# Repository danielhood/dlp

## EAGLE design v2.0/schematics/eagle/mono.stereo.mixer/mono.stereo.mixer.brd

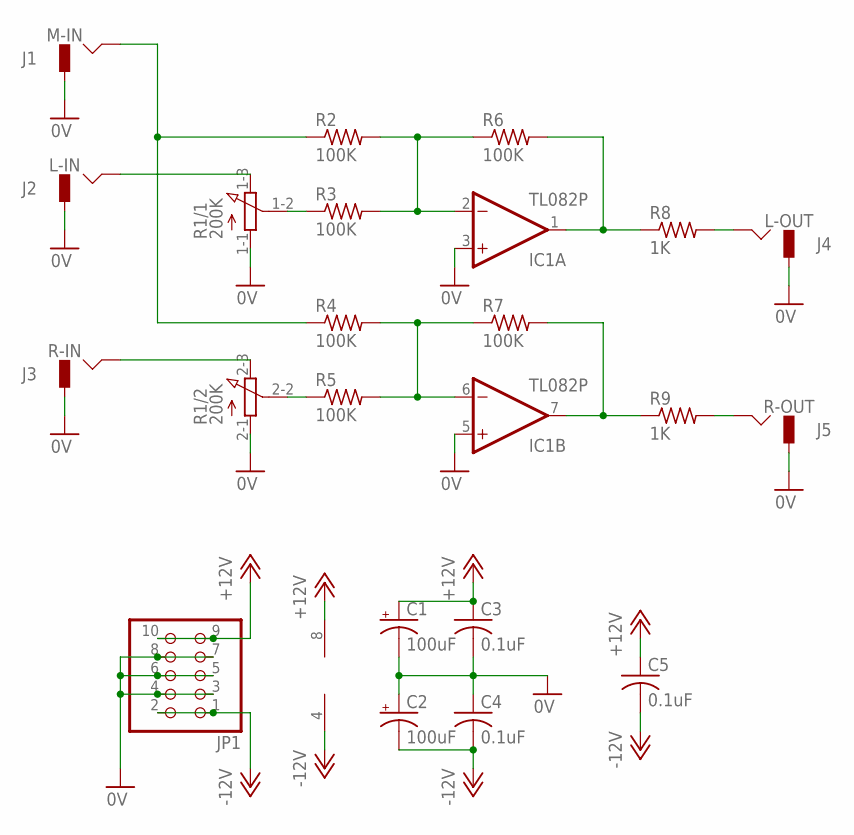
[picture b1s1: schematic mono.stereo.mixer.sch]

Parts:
C1, C2: 100uF; E2-5
C3, C4, C5: 0.1uF; C025-024X044
IC1: TL082P; DIL08
J1: M-IN; JACK-M
J2: L-IN; JACK-M
J3: R-IN; JACK-M
J4: L-OUT; JACK-M
J5: R-OUT; JACK-M
JP1: PINHD-2X5; 2X05
R1: 200K; 3RP/1610G
R2, R3, R4, R5, R6, R7: 100K; 0204/5
R8, R9: 1K; 0204/5

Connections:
0V: C1.-, C2.+, C3.2, C4.1, IC1.3 (+IN), IC1.5 (+IN), J1.GND, J2.GND, J3.GND, J4.GND, J5.GND, JP1.3, JP1.4, JP1.5, JP1.6, JP1.7, JP1.8, R1.1-1 (A), R1.2-1 (A)
+12V: C1.+, C3.1, C5.1, IC1.8 (V+), JP1.9, JP1.10
-12V: C2.-, C4.2, C5.2, IC1.4 (V-), JP1.1, JP1.2
unnamed: J1.HOT, R2.1, R4.1
unnamed: IC1.2 (-IN), R2.2, R3.2, R6.1
unnamed: IC1.6 (-IN), R4.2, R5.2, R7.1
unnamed: IC1.1 (OUT), R6.2, R8.1
unnamed: J4.HOT, R8.2
unnamed: IC1.7 (OUT), R7.2, R9.1
unnamed: J5.HOT, R9.2
unnamed: J2.HOT, R1.1-3 (E)
unnamed: J3.HOT, R1.2-3 (E)
unnamed: R1.2-2 (S), R5.1
unnamed: R1.1-2 (S), R3.1

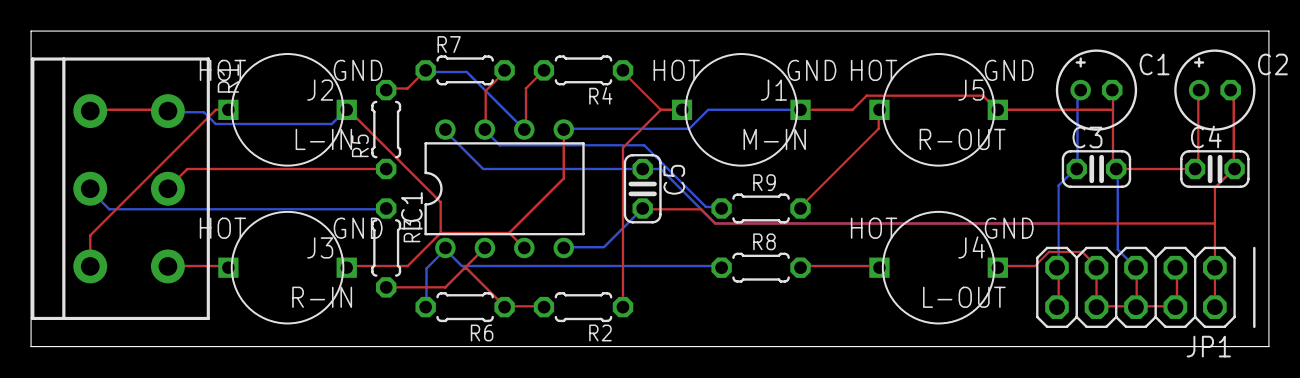
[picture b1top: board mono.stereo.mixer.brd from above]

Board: 2 copper layers, 79.7 x 20.3 mm, 21 parts (0 on the bottom side), 14 nets.

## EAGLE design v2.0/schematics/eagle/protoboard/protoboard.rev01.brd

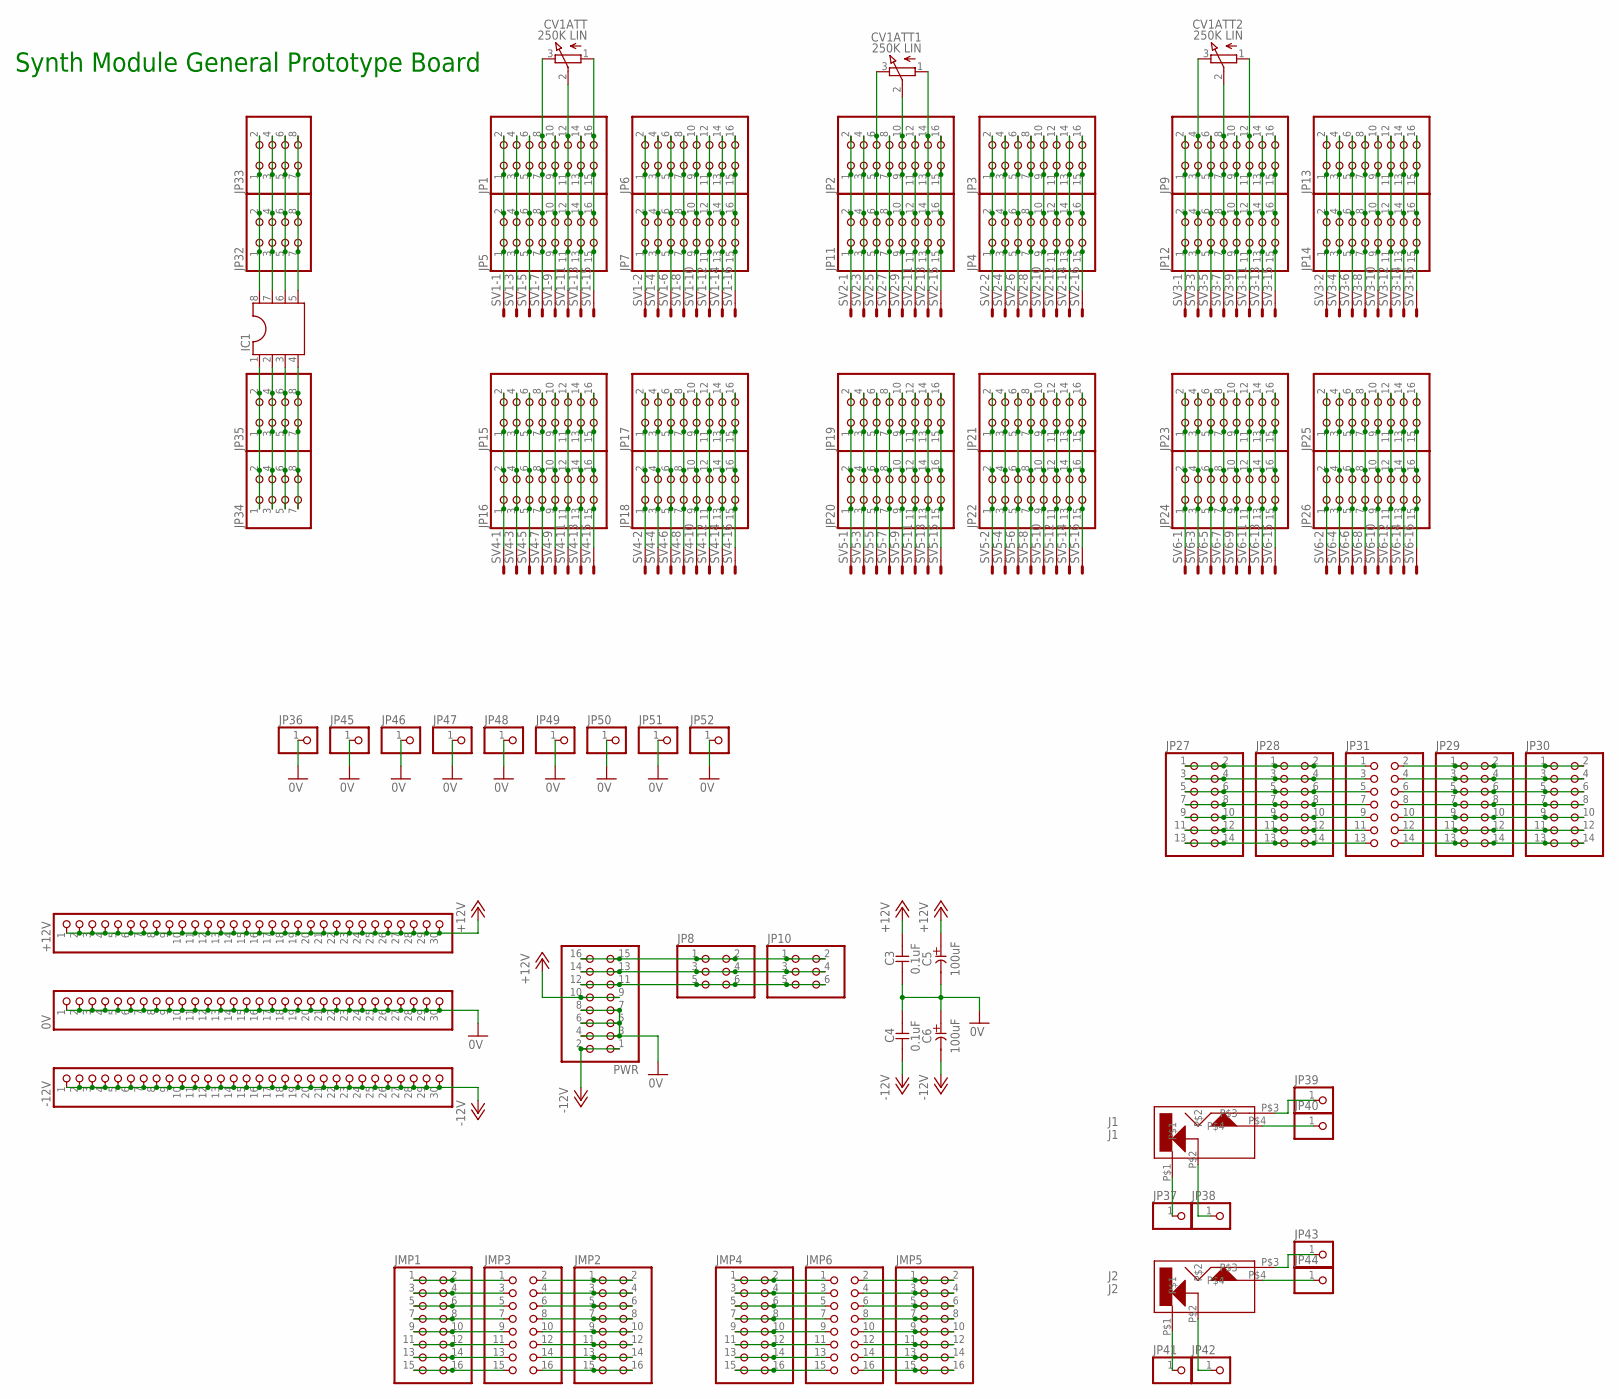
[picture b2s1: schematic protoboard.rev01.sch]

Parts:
0V: PINHD-1X30; 1X30
+12V: PINHD-1X30; 1X30
-12V: PINHD-1X30; 1X30
C3, C4: 0.1uF; C025-024X044
C5, C6: 100uF; E5-8,5
CV1ATT, CV1ATT1, CV1ATT2: 250K LIN; 3RP/1610N
IC1: DIL8S; SOCKET-08
J1: J1; CL1384
J2: J2; CL1384
JMP1, JMP2, JMP3, JMP4, JMP5, JMP6: PINHD-2X8; 2X08
JP1, JP2, JP3, JP4, JP5, JP6, JP7, JP9, JP11, JP12, JP13, JP14, JP15, JP16, JP17, JP18, JP19, JP20, JP21, JP22, JP23, JP24, JP25, JP26: PINHD-2X8; 2X08
JP8, JP10: PINHD-2X3; 2X03
JP27, JP28, JP29, JP30, JP31: PINHD-2X7; 2X07
JP32, JP33, JP34, JP35: PINHD-2X4; 2X04
JP36, JP37, JP38, JP39, JP40, JP41, JP42, JP43, JP44, JP45, JP46, JP47, JP48, JP49, JP50, JP51, JP52: PINHD-1X1; 1X01
PWR: PINHD-2X8; 2X08
SV1, SV2, SV3, SV4, SV5, SV6: 16E; 16P

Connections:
0V: 0V.1, 0V.2, 0V.3, 0V.4, 0V.5, 0V.6, 0V.7, 0V.8, 0V.9, 0V.10, 0V.11, 0V.12, 0V.13, 0V.14, 0V.15, 0V.16, 0V.17, 0V.18, 0V.19, 0V.20, 0V.21, 0V.22, 0V.23, 0V.24, 0V.25, 0V.26, 0V.27, 0V.28, 0V.29, 0V.30, C3.2, C4.1, C5.-, C6.+, JP36.1, JP45.1, JP46.1, JP47.1, JP48.1, JP49.1, JP50.1, JP51.1, JP52.1, PWR.3, PWR.4, PWR.5, PWR.6, PWR.7, PWR.8
+12V: +12V.1, +12V.2, +12V.3, +12V.4, +12V.5, +12V.6, +12V.7, +12V.8, +12V.9, +12V.10, +12V.11, +12V.12, +12V.13, +12V.14, +12V.15, +12V.16, +12V.17, +12V.18, +12V.19, +12V.20, +12V.21, +12V.22, +12V.23, +12V.24, +12V.25, +12V.26, +12V.27, +12V.28, +12V.29, +12V.30, C3.1, C5.+, PWR.9, PWR.10
-12V: -12V.1, -12V.2, -12V.3, -12V.4, -12V.5, -12V.6, -12V.7, -12V.8, -12V.9, -12V.10, -12V.11, -12V.12, -12V.13, -12V.14, -12V.15, -12V.16, -12V.17, -12V.18, -12V.19, -12V.20, -12V.21, -12V.22, -12V.23, -12V.24, -12V.25, -12V.26, -12V.27, -12V.28, -12V.29, -12V.30, C4.2, C6.-, PWR.1, PWR.2
unnamed: JP2.1, JP2.2, JP11.1, JP11.2, SV2.1
unnamed: JP3.1, JP3.2, JP4.1, JP4.2, SV2.2
unnamed: JP2.3, JP2.4, JP11.3, JP11.4, SV2.3
unnamed: CV1ATT1.3 (E), JP2.5, JP2.6, JP11.5, JP11.6, SV2.5
unnamed: JP2.7, JP2.8, JP11.7, JP11.8, SV2.7
unnamed: CV1ATT1.2 (S), JP2.9, JP2.10, JP11.9, JP11.10, SV2.9
unnamed: JP2.11, JP2.12, JP11.11, JP11.12, SV2.11
unnamed: CV1ATT1.1 (A), JP2.13, JP2.14, JP11.13, JP11.14, SV2.13
unnamed: JP3.3, JP3.4, JP4.3, JP4.4, SV2.4
unnamed: JP3.5, JP3.6, JP4.5, JP4.6, SV2.6
unnamed: JP3.7, JP3.8, JP4.7, JP4.8, SV2.8
unnamed: JP3.9, JP3.10, JP4.9, JP4.10, SV2.10
unnamed: JP3.11, JP3.12, JP4.11, JP4.12, SV2.12
unnamed: JP3.13, JP3.14, JP4.13, JP4.14, SV2.14
unnamed: JP3.15, JP3.16, JP4.15, JP4.16, SV2.16
unnamed: JP1.1, JP1.2, JP5.1, JP5.2, SV1.1
unnamed: JP1.3, JP1.4, JP5.3, JP5.4, SV1.3
unnamed: JP1.5, JP1.6, JP5.5, JP5.6, SV1.5
unnamed: CV1ATT.3 (E), JP1.7, JP1.8, JP5.7, JP5.8, SV1.7
unnamed: JP1.9, JP1.10, JP5.9, JP5.10, SV1.9
unnamed: CV1ATT.2 (S), JP1.11, JP1.12, JP5.11, JP5.12, SV1.11
unnamed: JP1.13, JP1.14, JP5.13, JP5.14, SV1.13
unnamed: CV1ATT.1 (A), JP1.15, JP1.16, JP5.15, JP5.16, SV1.15
unnamed: JP6.1, JP6.2, JP7.1, JP7.2, SV1.2
unnamed: JP6.3, JP6.4, JP7.3, JP7.4, SV1.4
unnamed: JP6.5, JP6.6, JP7.5, JP7.6, SV1.6
unnamed: JP6.7, JP6.8, JP7.7, JP7.8, SV1.8
unnamed: JP6.9, JP6.10, JP7.9, JP7.10, SV1.10
unnamed: JP6.11, JP6.12, JP7.11, JP7.12, SV1.12
unnamed: JP2.15, JP2.16, JP11.15, JP11.16, SV2.15
unnamed: JP6.13, JP6.14, JP7.13, JP7.14, SV1.14
unnamed: JP6.15, JP6.16, JP7.15, JP7.16, SV1.16
unnamed: JP9.1, JP9.2, JP12.1, JP12.2, SV3.1
unnamed: CV1ATT2.3 (E), JP9.3, JP9.4, JP12.3, JP12.4, SV3.3
unnamed: JP9.5, JP9.6, JP12.5, JP12.6, SV3.5
unnamed: CV1ATT2.2 (S), JP9.7, JP9.8, JP12.7, JP12.8, SV3.7
unnamed: JP9.9, JP9.10, JP12.9, JP12.10, SV3.9
unnamed: CV1ATT2.1 (A), JP9.11, JP9.12, JP12.11, JP12.12, SV3.11
unnamed: JP9.13, JP9.14, JP12.13, JP12.14, SV3.13
unnamed: JP9.15, JP9.16, JP12.15, JP12.16, SV3.15
unnamed: JP13.1, JP13.2, JP14.1, JP14.2, SV3.2
unnamed: JP13.3, JP13.4, JP14.3, JP14.4, SV3.4
unnamed: JP13.5, JP13.6, JP14.5, JP14.6, SV3.6
unnamed: JP13.7, JP13.8, JP14.7, JP14.8, SV3.8
unnamed: JP13.9, JP13.10, JP14.9, JP14.10, SV3.10
unnamed: JP13.11, JP13.12, JP14.11, JP14.12, SV3.12
unnamed: JP13.13, JP13.14, JP14.13, JP14.14, SV3.14
unnamed: JP13.15, JP13.16, JP14.15, JP14.16, SV3.16
unnamed: JP15.1, JP15.2, JP16.1, JP16.2, SV4.1
unnamed: JP15.3, JP15.4, JP16.3, JP16.4, SV4.3
unnamed: JP15.5, JP15.6, JP16.5, JP16.6, SV4.5
unnamed: JP15.7, JP15.8, JP16.7, JP16.8, SV4.7
unnamed: JP15.9, JP15.10, JP16.9, JP16.10, SV4.9
unnamed: JP15.11, JP15.12, JP16.11, JP16.12, SV4.11
unnamed: JP15.13, JP15.14, JP16.13, JP16.14, SV4.13
unnamed: JP15.15, JP15.16, JP16.15, JP16.16, SV4.15
unnamed: JP17.1, JP17.2, JP18.1, JP18.2, SV4.2
unnamed: JP17.3, JP17.4, JP18.3, JP18.4, SV4.4
unnamed: JP17.5, JP17.6, JP18.5, JP18.6, SV4.6
unnamed: JP17.7, JP17.8, JP18.7, JP18.8, SV4.8
unnamed: JP17.9, JP17.10, JP18.9, JP18.10, SV4.10
unnamed: JP17.11, JP17.12, JP18.11, JP18.12, SV4.12
unnamed: JP17.13, JP17.14, JP18.13, JP18.14, SV4.14
unnamed: JP17.15, JP17.16, JP18.15, JP18.16, SV4.16
unnamed: JP19.1, JP19.2, JP20.1, JP20.2, SV5.1
unnamed: JP19.3, JP19.4, JP20.3, JP20.4, SV5.3
unnamed: JP19.5, JP19.6, JP20.5, JP20.6, SV5.5
unnamed: JP19.7, JP19.8, JP20.7, JP20.8, SV5.7
unnamed: JP19.9, JP19.10, JP20.9, JP20.10, SV5.9
unnamed: JP19.11, JP19.12, JP20.11, JP20.12, SV5.11
unnamed: JP19.13, JP19.14, JP20.13, JP20.14, SV5.13
unnamed: JP19.15, JP19.16, JP20.15, JP20.16, SV5.15
unnamed: JP21.1, JP21.2, JP22.1, JP22.2, SV5.2
unnamed: JP21.3, JP21.4, JP22.3, JP22.4, SV5.4
unnamed: JP21.5, JP21.6, JP22.5, JP22.6, SV5.6
unnamed: JP21.7, JP21.8, JP22.7, JP22.8, SV5.8
unnamed: JP21.9, JP21.10, JP22.9, JP22.10, SV5.10
unnamed: JP21.11, JP21.12, JP22.11, JP22.12, SV5.12
unnamed: JP21.13, JP21.14, JP22.13, JP22.14, SV5.14
unnamed: JP21.15, JP21.16, JP22.15, JP22.16, SV5.16
unnamed: JP23.1, JP23.2, JP24.1, JP24.2, SV6.1
unnamed: JP23.3, JP23.4, JP24.3, JP24.4, SV6.3
unnamed: JP23.5, JP23.6, JP24.5, JP24.6, SV6.5
unnamed: JP23.7, JP23.8, JP24.7, JP24.8, SV6.7
unnamed: JP23.9, JP23.10, JP24.9, JP24.10, SV6.9
unnamed: JP23.11, JP23.12, JP24.11, JP24.12, SV6.11
unnamed: JP23.13, JP23.14, JP24.13, JP24.14, SV6.13
unnamed: JP23.15, JP23.16, JP24.15, JP24.16, SV6.15
unnamed: JP25.1, JP25.2, JP26.1, JP26.2, SV6.2
unnamed: JP25.3, JP25.4, JP26.3, JP26.4, SV6.4
unnamed: JP25.5, JP25.6, JP26.5, JP26.6, SV6.6
unnamed: JP25.7, JP25.8, JP26.7, JP26.8, SV6.8
unnamed: JP25.9, JP25.10, JP26.9, JP26.10, SV6.10
unnamed: JP25.11, JP25.12, JP26.11, JP26.12, SV6.12
unnamed: JP25.13, JP25.14, JP26.13, JP26.14, SV6.14
unnamed: JP25.15, JP25.16, JP26.15, JP26.16, SV6.16
unnamed: J1.P$1, JP37.1
unnamed: J1.P$2, JP38.1
unnamed: J2.P$1, JP41.1
unnamed: J2.P$2, JP42.1
unnamed: JMP1.1, JMP1.2, JMP3.1
unnamed: JMP1.3, JMP1.4, JMP3.3
unnamed: JMP1.5, JMP1.6, JMP3.5
unnamed: JMP1.7, JMP1.8, JMP3.7
unnamed: JMP1.9, JMP1.10, JMP3.9
unnamed: JMP1.11, JMP1.12, JMP3.11
unnamed: JMP1.13, JMP1.14, JMP3.13
unnamed: JMP1.15, JMP1.16, JMP3.15
unnamed: JMP2.1, JMP2.2, JMP3.2
unnamed: JMP2.3, JMP2.4, JMP3.4
unnamed: JMP2.5, JMP2.6, JMP3.6
unnamed: JMP2.7, JMP2.8, JMP3.8
unnamed: JMP2.9, JMP2.10, JMP3.10
unnamed: JMP2.11, JMP2.12, JMP3.12
unnamed: JMP2.13, JMP2.14, JMP3.14
unnamed: JMP2.15, JMP2.16, JMP3.16
unnamed: JMP4.1, JMP4.2, JMP6.1
unnamed: JMP4.3, JMP4.4, JMP6.3
unnamed: JMP4.5, JMP4.6, JMP6.5
unnamed: JMP4.7, JMP4.8, JMP6.7
unnamed: JMP4.9, JMP4.10, JMP6.9
unnamed: JMP4.11, JMP4.12, JMP6.11
unnamed: JMP4.13, JMP4.14, JMP6.13
unnamed: JMP4.15, JMP4.16, JMP6.15
unnamed: JMP5.1, JMP5.2, JMP6.2
unnamed: JMP5.3, JMP5.4, JMP6.4
unnamed: JMP5.5, JMP5.6, JMP6.6
unnamed: JMP5.7, JMP5.8, JMP6.8
unnamed: JMP5.9, JMP5.10, JMP6.10
unnamed: JMP5.11, JMP5.12, JMP6.12
unnamed: JMP5.13, JMP5.14, JMP6.14
unnamed: JMP5.15, JMP5.16, JMP6.16
unnamed: JP27.1, JP27.2, JP28.1, JP28.2, JP31.1
unnamed: JP27.3, JP27.4, JP28.3, JP28.4, JP31.3
unnamed: JP27.5, JP27.6, JP28.5, JP28.6, JP31.5
unnamed: JP27.7, JP27.8, JP28.7, JP28.8, JP31.7
unnamed: JP27.9, JP27.10, JP28.9, JP28.10, JP31.9
unnamed: JP27.11, JP27.12, JP28.11, JP28.12, JP31.11
unnamed: JP27.13, JP27.14, JP28.13, JP28.14, JP31.13
unnamed: IC1.8, JP32.1, JP32.2, JP33.1, JP33.2
unnamed: IC1.7, JP32.3, JP32.4, JP33.3, JP33.4
unnamed: IC1.6, JP32.5, JP32.6, JP33.5, JP33.6
unnamed: IC1.5, JP32.7, JP32.8, JP33.7, JP33.8
unnamed: J2.P$3, JP43.1
unnamed: J2.P$4, JP44.1
unnamed: J1.P$4, JP40.1
unnamed: JP29.1, JP29.2, JP30.1, JP30.2, JP31.2
unnamed: JP29.3, JP29.4, JP30.3, JP30.4, JP31.4
unnamed: JP29.5, JP29.6, JP30.5, JP30.6, JP31.6
unnamed: JP29.7, JP29.8, JP30.7, JP30.8, JP31.8
unnamed: JP29.9, JP29.10, JP30.9, JP30.10, JP31.10
unnamed: JP29.11, JP29.12, JP30.11, JP30.12, JP31.12
unnamed: JP29.13, JP29.14, JP30.13, JP30.14, JP31.14
unnamed: J1.P$3, JP39.1
unnamed: IC1.1, JP34.1, JP34.2, JP35.1, JP35.2
unnamed: IC1.2, JP34.3, JP34.4, JP35.3, JP35.4
unnamed: IC1.3, JP34.5, JP34.6, JP35.5, JP35.6
unnamed: IC1.4, JP34.7, JP34.8, JP35.7, JP35.8
unnamed: JP8.5, JP8.6, JP10.5, JP10.6, PWR.11, PWR.12
unnamed: JP8.1, JP8.2, JP10.1, JP10.2, PWR.15, PWR.16
unnamed: JP8.3, JP8.4, JP10.3, JP10.4, PWR.13, PWR.14

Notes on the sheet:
Synth Module General Prototype Board

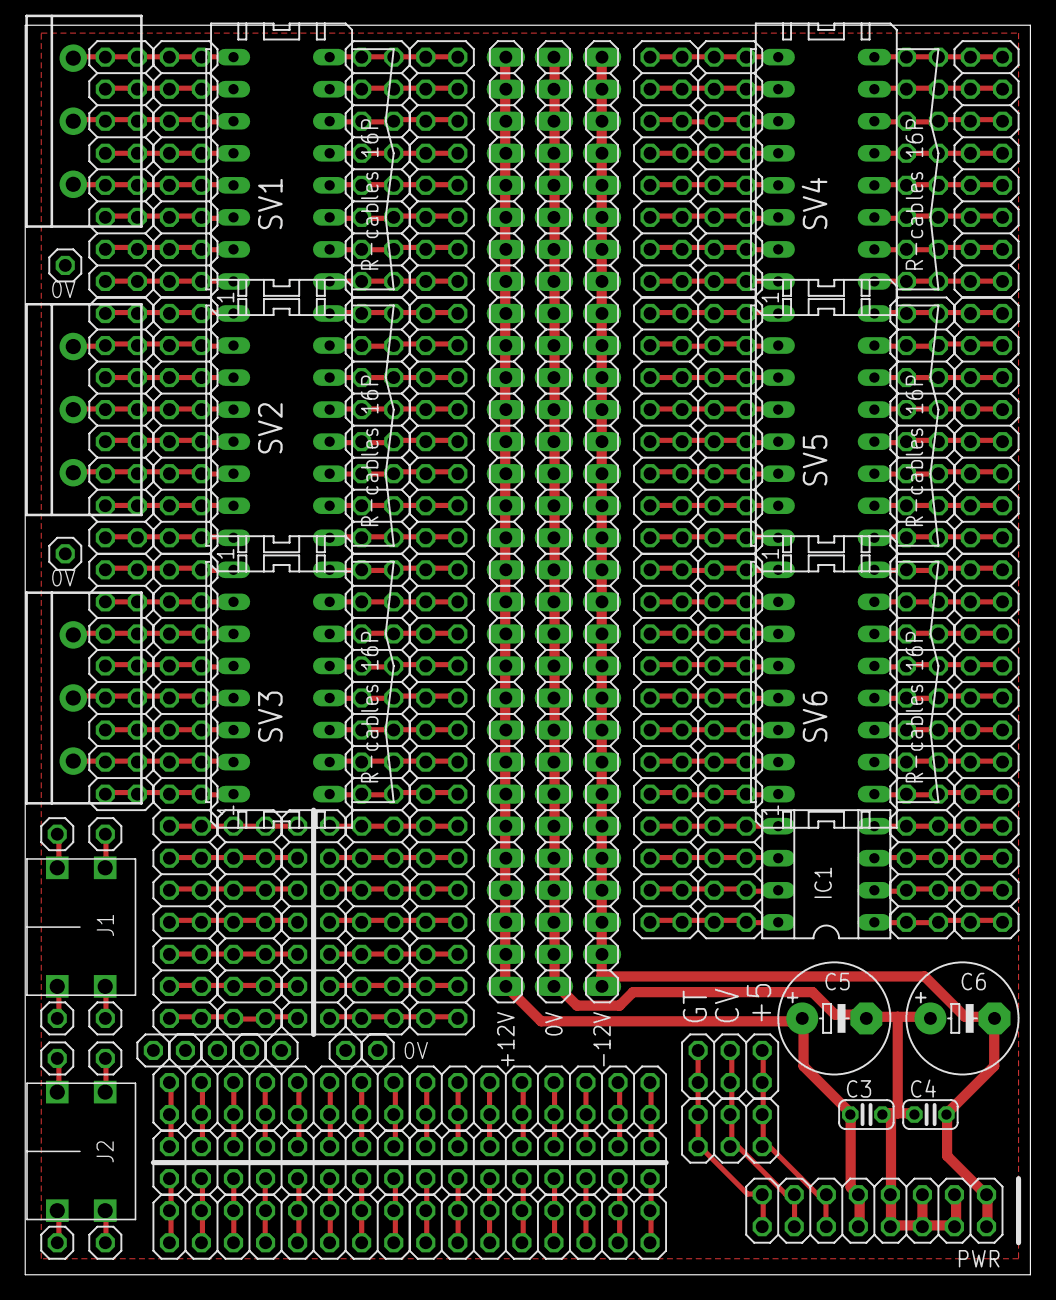
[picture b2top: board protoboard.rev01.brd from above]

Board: 2 copper layers, 79.7 x 99.0 mm, 78 parts (1 on the bottom side), 164 nets.

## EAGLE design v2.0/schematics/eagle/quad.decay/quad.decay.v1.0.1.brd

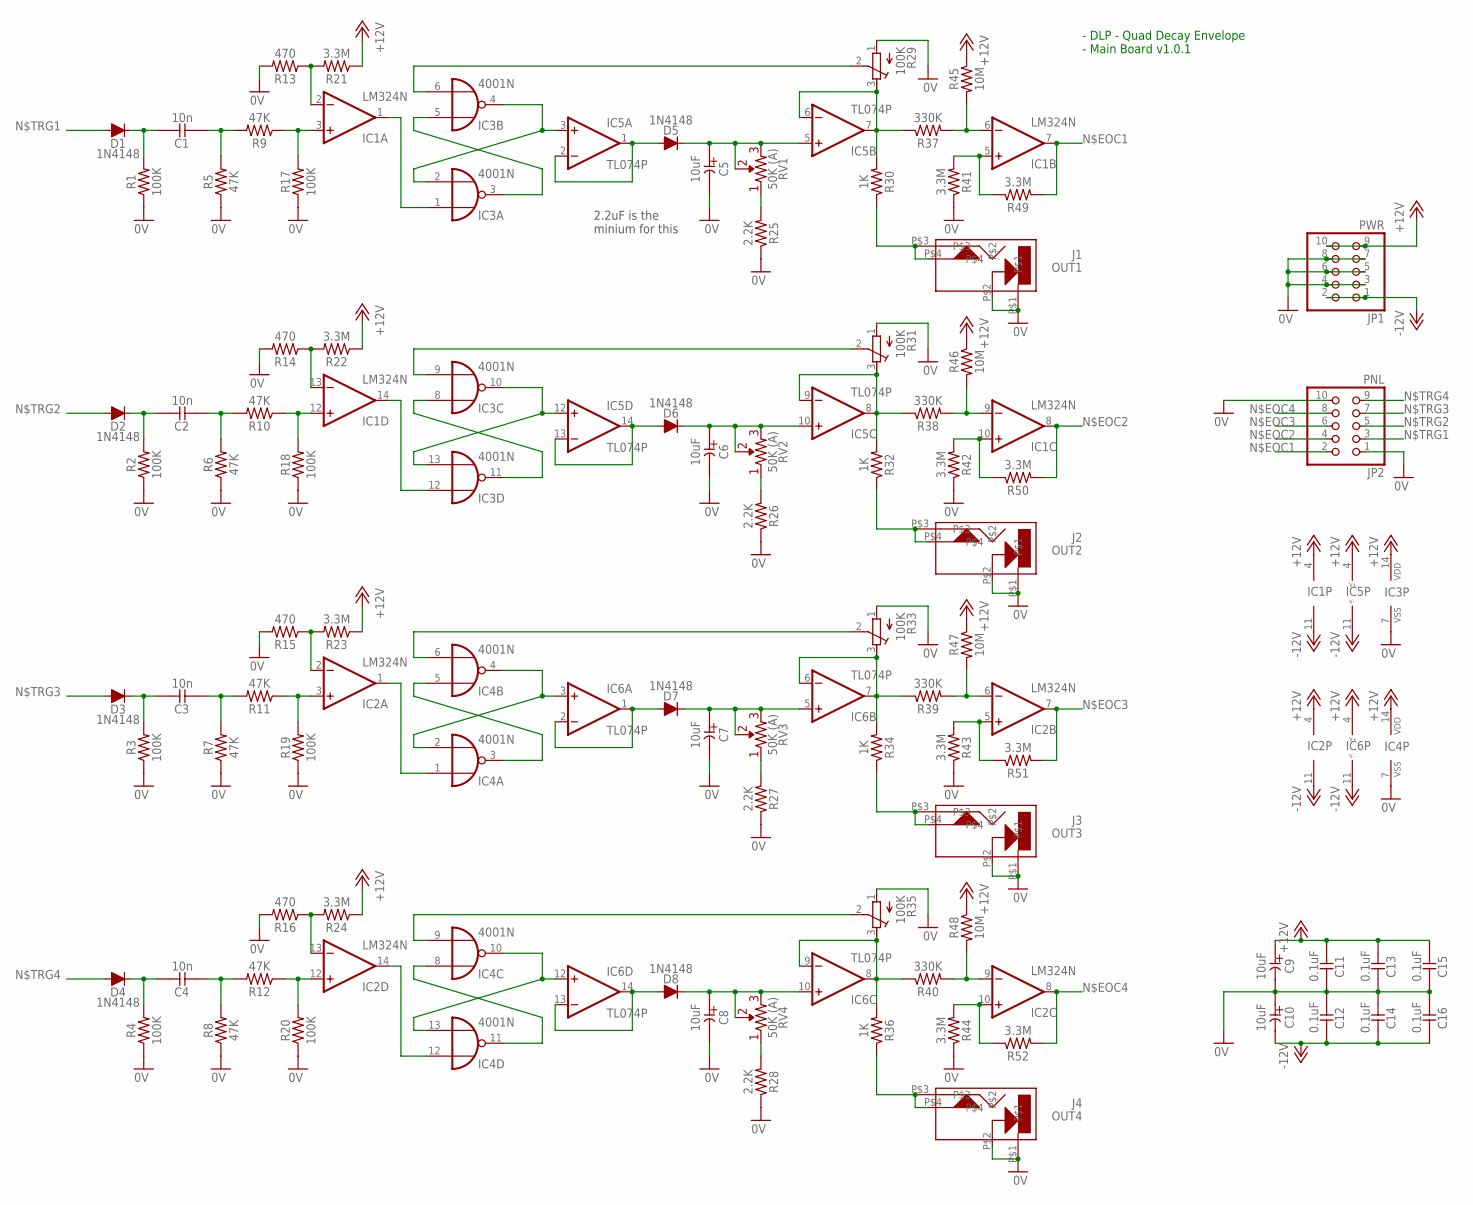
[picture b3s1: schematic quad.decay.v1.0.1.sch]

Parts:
C1, C2, C3, C4: 10n; C025-024X044
C5, C6, C7, C8, C9, C10: 10uF; E2-5
C11, C12, C13, C14, C15, C16: 0.1uF; C025-024X044
D1, D2, D3, D4, D5, D6, D7, D8: 1N4148; DO34-5
IC1, IC2: LM324N; DIL14
IC3, IC4: 4001N; DIL14
IC5, IC6: TL074P; DIL14
J1: OUT1; CL1384
J2: OUT2; CL1384
J3: OUT3; CL1384
J4: OUT4; CL1384
JP1: PWR; 2X05
JP2: PNL; 2X05
R1, R2, R3, R4, R17, R18, R19, R20: 100K; 0207/7
R5, R6, R7, R8, R9, R10, R11, R12: 47K; 0207/7
R13, R14, R15, R16: 470; 0207/7
R21, R22, R23, R24, R41, R42, R43, R44, R49, R50, R51, R52: 3.3M; 0207/7
R25, R26, R27, R28: 2.2K; 0207/7
R29, R31, R33, R35: 100K; RTRIM3339P
R30, R32, R34, R36: 1K; 0207/7
R37, R38, R39, R40: 330K; 0207/7
R45, R46, R47, R48: 10M; 0207/7
RV1, RV2, RV3, RV4: 50K (A); R-VAR

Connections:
0V: C5.-, C6.-, C7.-, C8.-, C9.-, C10.+, C11.1, C12.2, C13.1, C14.2, C15.1, C16.2, IC3.7 (VSS), IC4.7 (VSS), J1.P$1, J1.P$2, J2.P$1, J2.P$2, J3.P$1, J3.P$2, J4.P$1, J4.P$2, JP1.3, JP1.4, JP1.5, JP1.6, JP1.7, JP1.8, JP2.1, JP2.10, R1.1, R2.1, R3.1, R4.1, R5.1, R6.1, R7.1, R8.1, R13.2, R14.2, R15.2, R16.2, R17.1, R18.1, R19.1, R20.1, R25.1, R26.1, R27.1, R28.1, R29.1 (A), R31.1 (A), R33.1 (A), R35.1 (A), R41.1, R42.1, R43.1, R44.1
+12V: C9.+, C11.2, C13.2, C15.2, IC1.4 (V+), IC2.4 (V+), IC3.14 (VDD), IC4.14 (VDD), IC5.4 (V+), IC6.4 (V+), JP1.9, JP1.10, R21.1, R22.1, R23.1, R24.1, R45.1, R46.1, R47.1, R48.1
-12V: C10.-, C12.1, C14.1, C16.1, IC1.11 (V-), IC2.11 (V-), IC5.11 (V-), IC6.11 (V-), JP1.1, JP1.2
unnamed: R25.2, RV1.R1 (1)
unnamed: IC1.6 (-IN), R37.2, R45.2
unnamed: IC1.5 (+IN), R41.2, R49.1
unnamed: IC3.3 (O), IC3.5 (I0)
unnamed: IC3.8 (I0), IC3.11 (O)
unnamed: IC3.10 (O), IC3.13 (I1), IC5.12 (+IN)
unnamed: C2.1, D2.C, R2.2
unnamed: C2.2, R6.2, R10.2
unnamed: IC1.12 (+IN), R10.1, R18.2
unnamed: IC3.2 (I1), IC3.4 (O), IC5.3 (+IN)
unnamed: IC1.13 (-IN), R14.1, R22.2
unnamed: D5.A, IC5.1 (OUT), IC5.2 (-IN)
unnamed: C1.1, D1.C, R1.2
unnamed: C1.2, R5.2, R9.2
unnamed: IC1.3 (+IN), R9.1, R17.2
unnamed: IC1.2 (-IN), R13.1, R21.2
unnamed: IC1.1 (OUT), IC3.1 (I0)
unnamed: IC5.6 (-IN), IC5.7 (OUT), R29.3 (E), R30.2, R37.1
unnamed: J1.P$3, J1.P$4, R30.1
unnamed: IC3.6 (I1), R29.2 (S)
unnamed: IC1.14 (OUT), IC3.12 (I0)
unnamed: D6.A, IC5.13 (-IN), IC5.14 (OUT)
unnamed: IC5.8 (OUT), IC5.9 (-IN), R31.3 (E), R32.2, R38.1
unnamed: J2.P$3, J2.P$4, R32.1
unnamed: IC3.9 (I1), R31.2 (S)
unnamed: C6.+, D6.C, IC5.10 (+IN), RV2.R2 (2), RV2.VAR
unnamed: R26.2, RV2.R1 (1)
unnamed: IC1.9 (-IN), R38.2, R46.2
unnamed: IC1.10 (+IN), R42.2, R50.1
unnamed: IC4.3 (O), IC4.5 (I0)
unnamed: IC4.2 (I1), IC4.4 (O), IC6.3 (+IN)
unnamed: C3.1, D3.C, R3.2
unnamed: C3.2, R7.2, R11.2
unnamed: IC2.3 (+IN), R11.1, R19.2
unnamed: IC2.2 (-IN), R15.1, R23.2
unnamed: IC2.1 (OUT), IC4.1 (I0)
unnamed: D7.A, IC6.1 (OUT), IC6.2 (-IN)
unnamed: IC6.6 (-IN), IC6.7 (OUT), R33.3 (E), R34.2, R39.1
unnamed: J3.P$3, J3.P$4, R34.1
unnamed: IC4.6 (I1), R33.2 (S)
unnamed: C7.+, D7.C, IC6.5 (+IN), RV3.R2 (2), RV3.VAR
unnamed: R27.2, RV3.R1 (1)
unnamed: IC2.6 (-IN), R39.2, R47.2
unnamed: IC2.5 (+IN), R43.2, R51.1
unnamed: IC4.8 (I0), IC4.11 (O)
unnamed: IC4.10 (O), IC4.13 (I1), IC6.12 (+IN)
unnamed: C4.1, D4.C, R4.2
unnamed: C4.2, R8.2, R12.2
unnamed: IC2.12 (+IN), R12.1, R20.2
unnamed: C5.+, D5.C, IC5.5 (+IN), RV1.R2 (2), RV1.VAR
unnamed: IC2.13 (-IN), R16.1, R24.2
unnamed: IC2.14 (OUT), IC4.12 (I0)
unnamed: D8.A, IC6.13 (-IN), IC6.14 (OUT)
unnamed: IC6.8 (OUT), IC6.9 (-IN), R35.3 (E), R36.2, R40.1
unnamed: J4.P$3, J4.P$4, R36.1
unnamed: IC4.9 (I1), R35.2 (S)
unnamed: C8.+, D8.C, IC6.10 (+IN), RV4.R2 (2), RV4.VAR
unnamed: R28.2, RV4.R1 (1)
unnamed: IC2.9 (-IN), R40.2, R48.2
unnamed: IC2.10 (+IN), R44.2, R52.1
N$EOC1: IC1.7 (OUT), JP2.2, R49.2
N$EOC2: IC1.8 (OUT), JP2.4, R50.2
N$EOC3: IC2.7 (OUT), JP2.6, R51.2
N$EOC4: IC2.8 (OUT), JP2.8, R52.2
N$TRG1: D1.A, JP2.3
N$TRG2: D2.A, JP2.5
N$TRG3: D3.A, JP2.7
N$TRG4: D4.A, JP2.9

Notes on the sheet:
- DLP - Quad Decay Envelope - Main Board v1.0.1
2.2uF is the minium for this

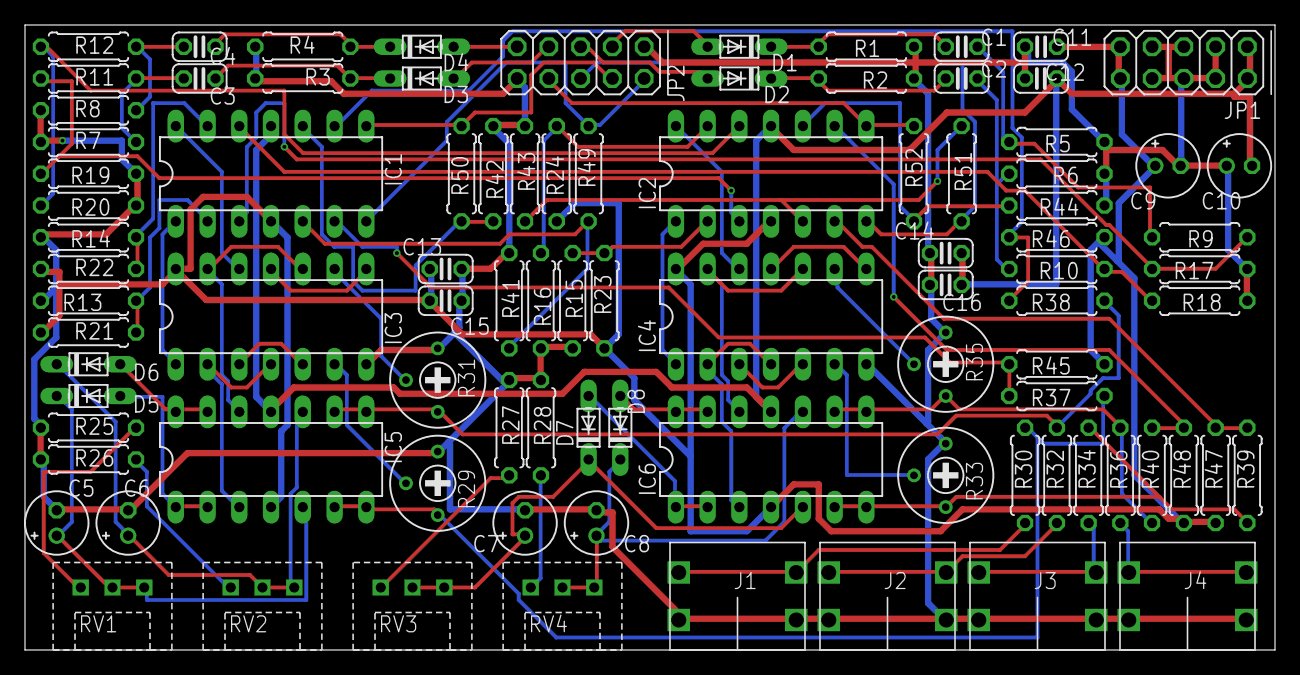
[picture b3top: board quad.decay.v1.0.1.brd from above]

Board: 2 copper layers, 100.0 x 50.0 mm, 92 parts (0 on the bottom side), 71 nets.

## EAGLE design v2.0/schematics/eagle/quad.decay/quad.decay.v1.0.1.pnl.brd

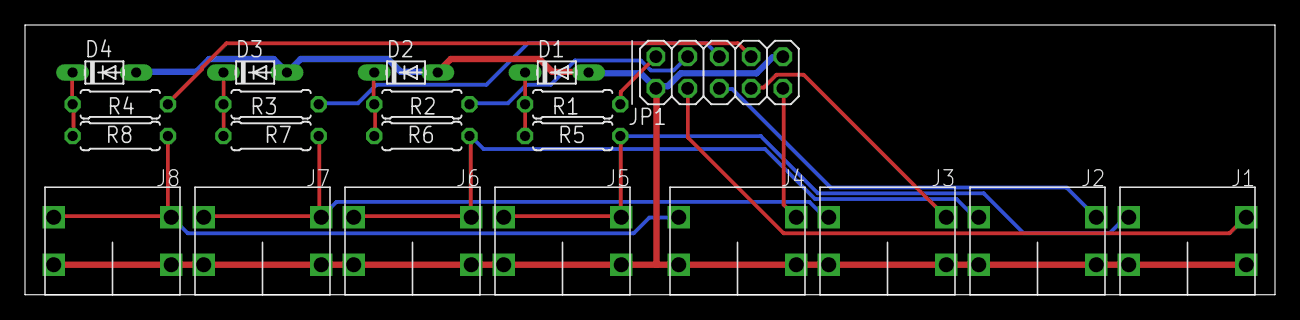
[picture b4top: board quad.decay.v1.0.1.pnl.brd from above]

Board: 2 copper layers, 100.0 x 21.6 mm, 21 parts (0 on the bottom side), 17 nets.

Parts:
D1, D2, D3, D4: 1N5232B; DO34-5
J1: TRG1; CL1384
J2: TRG2; CL1384
J3: TRG3; CL1384
J4: TRG4; CL1384
J5: EOC1; CL1384
J6: EOC2; CL1384
J7: EOC3; CL1384
J8: EOC4; CL1384
JP1: PNL; 2X05
R1, R2, R3, R4: 2.2K; 0207/7
R5, R6, R7, R8: 1K; 0207/7

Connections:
0V: D1.A, D2.A, D3.A, D4.A, J1.P$1, J1.P$2, J2.P$1, J2.P$2, J3.P$1, J3.P$2, J4.P$1, J4.P$2, J5.P$1, J5.P$2, J6.P$1, J6.P$2, J7.P$1, J7.P$2, J8.P$1, J8.P$2, JP1.1, JP1.10
unnamed: D1.C, R1.2, R5.1
unnamed: J1.P$4, J5.P$3, J5.P$4, R5.2
unnamed: D2.C, R2.2, R6.1
unnamed: D3.C, R3.2, R7.1
unnamed: D4.C, R4.2, R8.1
unnamed: J2.P$4, J6.P$3, J6.P$4, R6.2
unnamed: J3.P$4, J7.P$3, J7.P$4, R7.2
unnamed: J4.P$4, J8.P$3, J8.P$4, R8.2
N$EOC1: JP1.2, R1.1
N$EOC2: JP1.4, R2.1
N$EOC3: JP1.6, R3.1
N$EOC4: JP1.8, R4.1
N$TRG1: J1.P$3, JP1.3
N$TRG2: J2.P$3, JP1.5
N$TRG3: J3.P$3, JP1.7
N$TRG4: J4.P$3, JP1.9
